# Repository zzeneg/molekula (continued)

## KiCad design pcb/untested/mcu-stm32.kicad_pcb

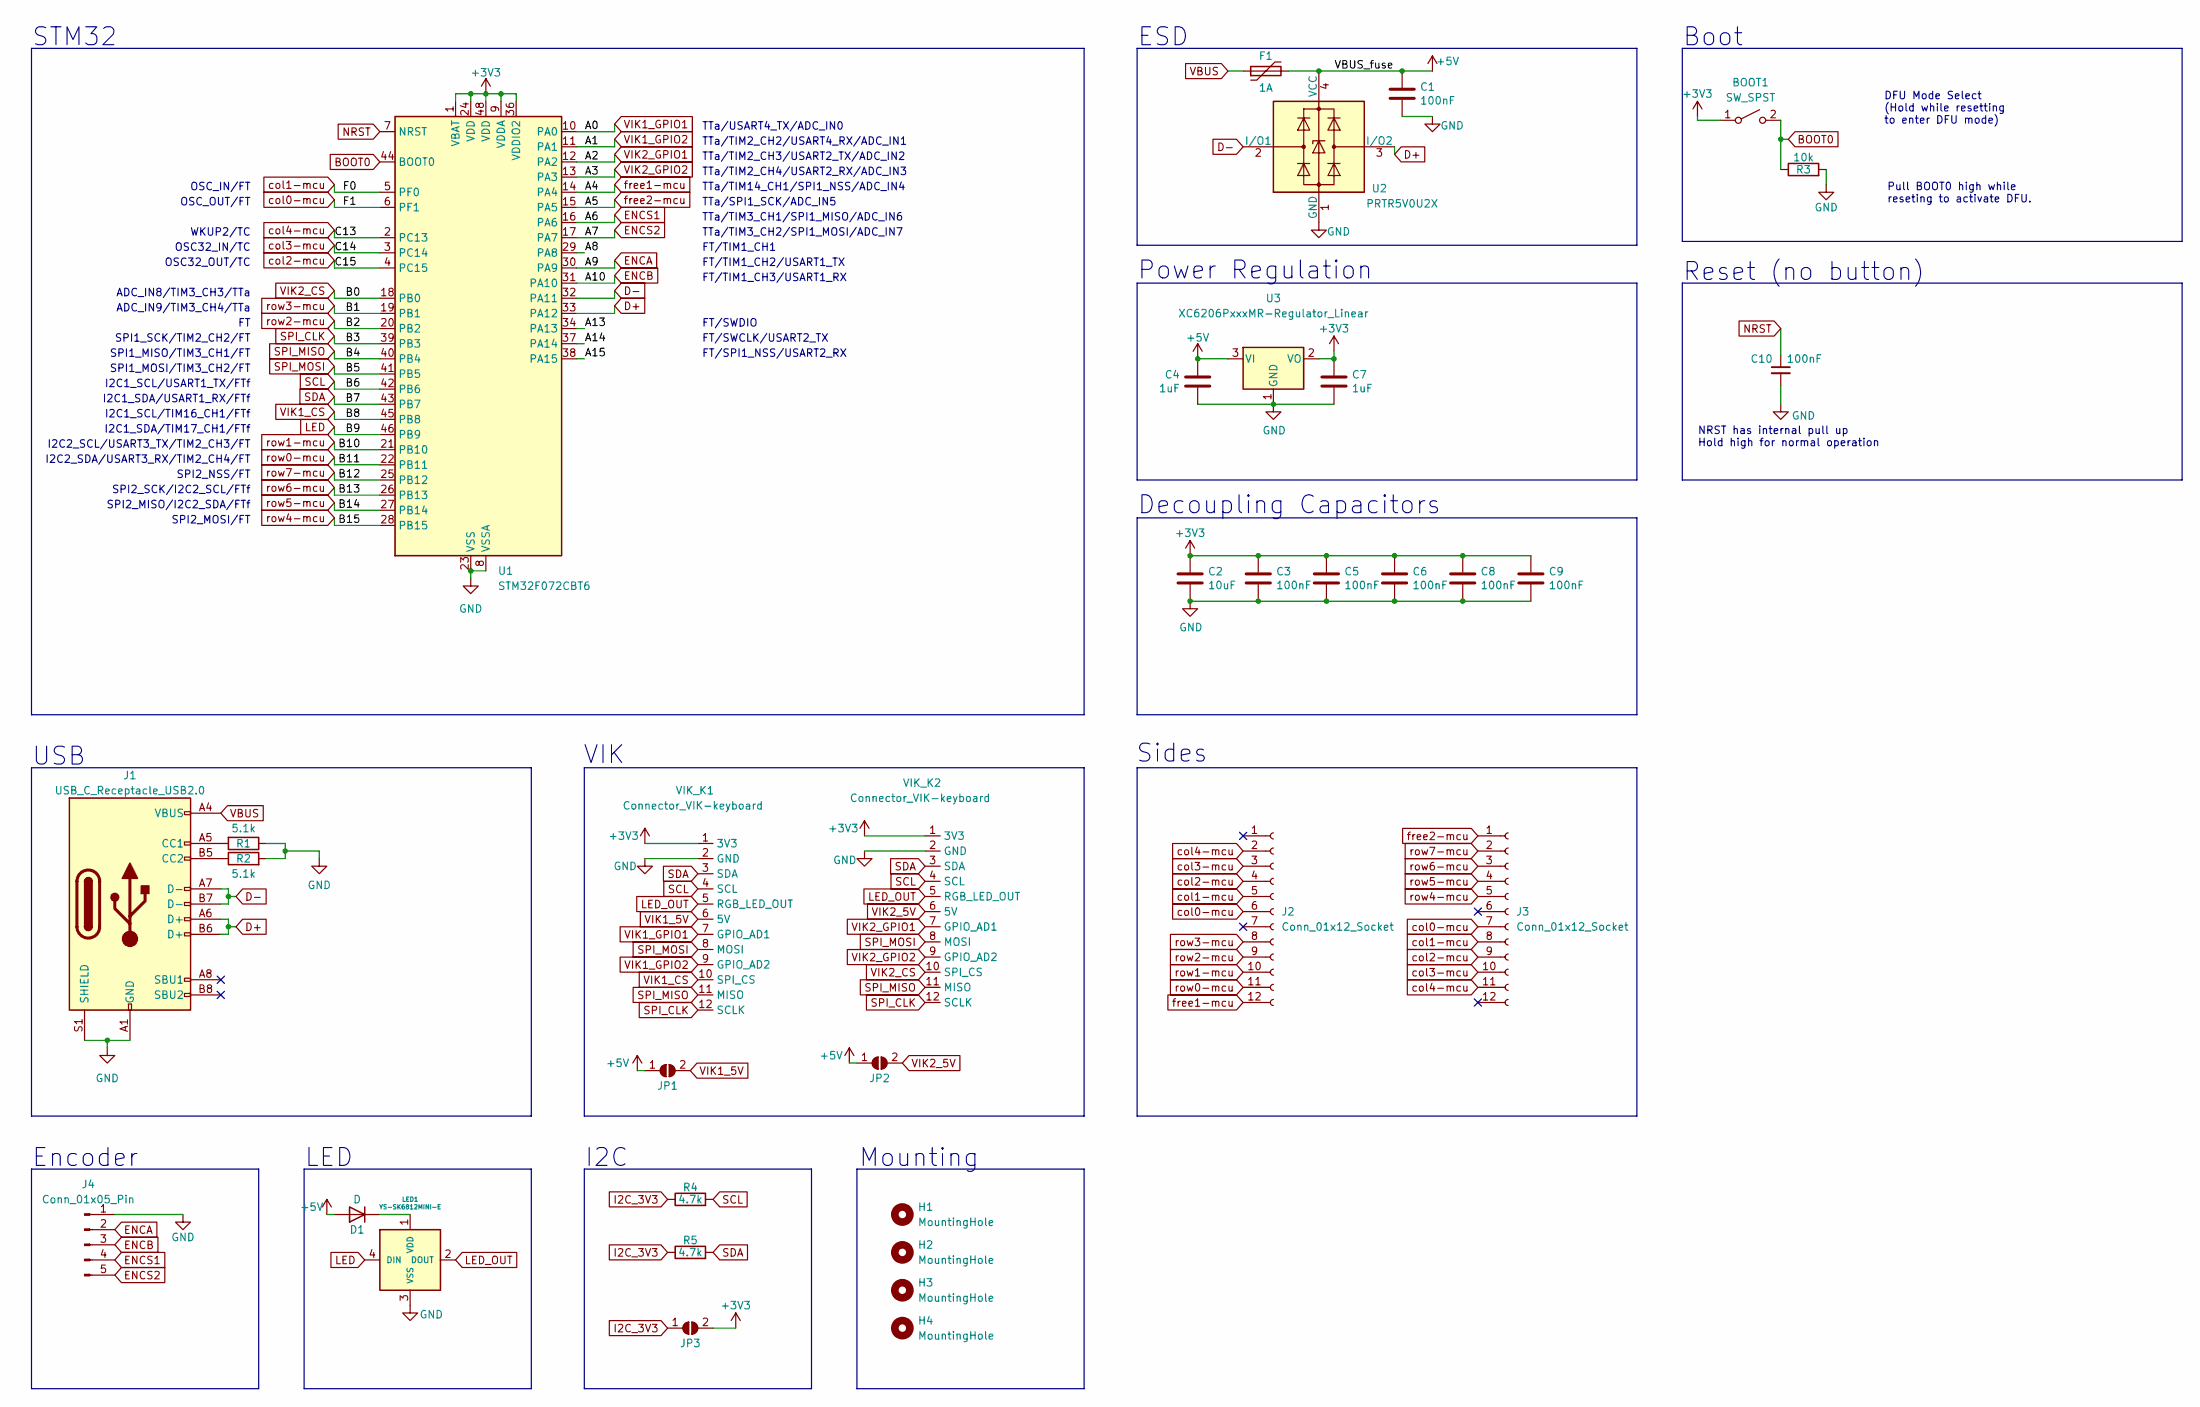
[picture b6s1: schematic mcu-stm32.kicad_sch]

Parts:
BOOT1: SW_SPST; SW_SPST_TL3342
C1, C3, C5, C6, C8, C9, C10: 100nF; C_0805_2012Metric; LCSC C307331
C2: 10uF; C_0805_2012Metric; LCSC C307331
C4, C7: 1uF; C_0805_2012Metric; LCSC C307331
D1: D; Diode_1N4148-SOD123
F1: 1A; Fuse_1206_3216Metric; LCSC C135341
H1, H2, H3, H4: MountingHole; Hole_M2
J1: USB_C_Receptacle_USB2.0; Connector_USB-C-mid-mount-ali; JlcRotOffset 180
J2, J3: Conn_01x12_Socket; Connector_FFC-12pin-0.5mm-horizontal
J4: Conn_01x05_Pin; PinSocket_1x05_P2.54mm_Vertical
JP1, JP2: 5V; SolderJumper-2_P1.3mm_Open_RoundedPad1.0x1.5mm
JP3: VCC; SolderJumper-2_P1.3mm_Open_RoundedPad1.0x1.5mm
LED1: YS-SK6812MINI-E; LED_SK6812-MINI-E
R1, R2: 5.1k; R_0805_2012Metric
R3: 10k; R_0805_2012Metric
R4, R5: 4.7k; R_0805_2012Metric
U1: STM32F072CBT6; LQFP-48_7x7mm_P0.5mm; JlcRotOffset 90
U2: PRTR5V0U2X; SOT-143; LCSC C2827688
U3: XC6206PxxxMR-Regulator_Linear; SOT-23; LCSC C5446
VIK_K1, VIK_K2: Connector_VIK-keyboard; Connector_VIK-horizontal-keyboard

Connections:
+3V3: BOOT1.1 (A), C2.1, C3.1, C5.1, C6.1, C7.1, C8.1, C9.1, JP3.2 (B), U1.1 (VBAT), U1.9 (VDDA), U1.24 (VDD), U1.36 (VDDIO2), U1.48 (VDD), U3.2 (VO), VIK_K1.1 (3V3), VIK_K2.1 (3V3)
+5V: C1.1, C4.1, D1.2 (A), F1.2, JP1.1 (A), JP2.1 (A), U2.4 (VCC), U3.3 (VI)
/A8: U1.29 (PA8)
/A13: U1.34 (PA13)
/A14: U1.37 (PA14)
/A15: U1.38 (PA15)
BOOT0: BOOT1.2 (B), R3.1, U1.44 (BOOT0)
D+: J1.A6 (D+), J1.B6 (D+), U1.33 (PA12), U2.3 (I/O2)
D-: J1.A7 (D-), J1.B7 (D-), U1.32 (PA11), U2.2 (I/O1)
ENCA: J4.2, U1.30 (PA9)
ENCB: J4.3, U1.31 (PA10)
ENCS1: J4.4, U1.16 (PA6)
ENCS2: J4.5, U1.17 (PA7)
GND: C1.2, C2.2, C3.2, C4.2, C5.2, C6.2, C7.2, C8.2, C9.2, C10.2, J1.A1 (GND), J1.A12 (GND), J1.B1 (GND), J1.B12 (GND), J1.S1 (SHIELD), J4.1, LED1.3 (VSS), R1.1, R2.2, R3.2, U1.8 (VSSA), U1.23 (VSS), U1.35 (VSS), U1.47 (VSS), U2.1 (GND), U3.1 (GND), VIK_K1.2 (GND), VIK_K2.2 (GND)
I2C_3V3: JP3.1 (A), R4.1, R5.1
LED: LED1.4 (DIN), U1.46 (PB9)
LED_OUT: LED1.2 (DOUT), VIK_K1.5 (RGB_LED_OUT), VIK_K2.5 (RGB_LED_OUT)
NRST: C10.1, U1.7 (NRST)
unnamed: D1.1 (K), LED1.1 (VDD)
unnamed: J1.A5 (CC1), R1.2
unnamed: J1.B5 (CC2), R2.1
SCL: R4.2, U1.42 (PB6), VIK_K1.4 (SCL), VIK_K2.4 (SCL)
SDA: R5.2, U1.43 (PB7), VIK_K1.3 (SDA), VIK_K2.3 (SDA)
SPI_CLK: U1.39 (PB3), VIK_K1.12 (SCLK), VIK_K2.12 (SCLK)
SPI_MISO: U1.40 (PB4), VIK_K1.11 (MISO), VIK_K2.11 (MISO)
SPI_MOSI: U1.41 (PB5), VIK_K1.8 (MOSI), VIK_K2.8 (MOSI)
VBUS: F1.1, J1.A4 (VBUS), J1.A9 (VBUS), J1.B4 (VBUS), J1.B9 (VBUS)
VIK1_5V: JP1.2 (B), VIK_K1.6 (5V)
VIK1_CS: U1.45 (PB8), VIK_K1.10 (SPI_CS)
VIK1_GPIO1: U1.10 (PA0), VIK_K1.7 (GPIO_AD1)
VIK1_GPIO2: U1.11 (PA1), VIK_K1.9 (GPIO_AD2)
VIK2_5V: JP2.2 (B), VIK_K2.6 (5V)
VIK2_CS: U1.18 (PB0), VIK_K2.10 (SPI_CS)
VIK2_GPIO1: U1.12 (PA2), VIK_K2.7 (GPIO_AD1)
VIK2_GPIO2: U1.13 (PA3), VIK_K2.9 (GPIO_AD2)
col0-mcu: J2.6, J3.7, U1.6 (PF1)
col1-mcu: J2.5, J3.8, U1.5 (PF0)
col2-mcu: J2.4, J3.9, U1.4 (PC15)
col3-mcu: J2.3, J3.10, U1.3 (PC14)
col4-mcu: J2.2, J3.11, U1.2 (PC13)
free1-mcu: J2.12, U1.14 (PA4)
free2-mcu: J3.1, U1.15 (PA5)
row0-mcu: J2.11, U1.22 (PB11)
row1-mcu: J2.10, U1.21 (PB10)
row2-mcu: J2.9, U1.20 (PB2)
row3-mcu: J2.8, U1.19 (PB1)
row4-mcu: J3.5, U1.28 (PB15)
row5-mcu: J3.4, U1.27 (PB14)
row6-mcu: J3.3, U1.26 (PB13)
row7-mcu: J3.2, U1.25 (PB12)

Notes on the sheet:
I2C
TTa/TIM2_CH2/USART4_RX/ADC_IN1
USB
SPI2_MISO/I2C2_SDA/FTf
TTa/TIM2_CH4/USART2_RX/ADC_IN3
I2C1_SCL/USART1_TX/FTf
TTa/TIM14_CH1/SPI1_NSS/ADC_IN4
Boot
SPI2_NSS/FT
TTa/TIM2_CH3/USART2_TX/ADC_IN2
OSC_OUT/FT
ADC_IN8/TIM3_CH3/TTa
WKUP2/TC
NRST has internal pull up Hold high for normal operation
DFU Mode Select (Hold while resetting to enter DFU mode)
FT/TIM1_CH2/USART1_TX
TTa/TIM3_CH1/SPI1_MISO/ADC_IN6
I2C1_SDA/TIM17_CH1/FTf
FT/TIM1_CH1
TTa/TIM3_CH2/SPI1_MOSI/ADC_IN7
Reset (no button)
SPI1_SCK/TIM2_CH2/FT
Encoder
Power Regulation
I2C2_SDA/USART3_RX/TIM2_CH4/FT
OSC32_OUT/TC
OSC32_IN/TC
SPI1_MOSI/TIM3_CH2/FT
Sides
FT/SWDIO
FT/SWCLK/USART2_TX
TTa/SPI1_SCK/ADC_IN5
VIK
I2C2_SCL/USART3_TX/TIM2_CH3/FT
SPI1_MISO/TIM3_CH1/FT
FT/SPI1_NSS/USART2_RX
SPI2_SCK/I2C2_SCL/FTf
LED
SPI2_MOSI/FT
OSC_IN/FT

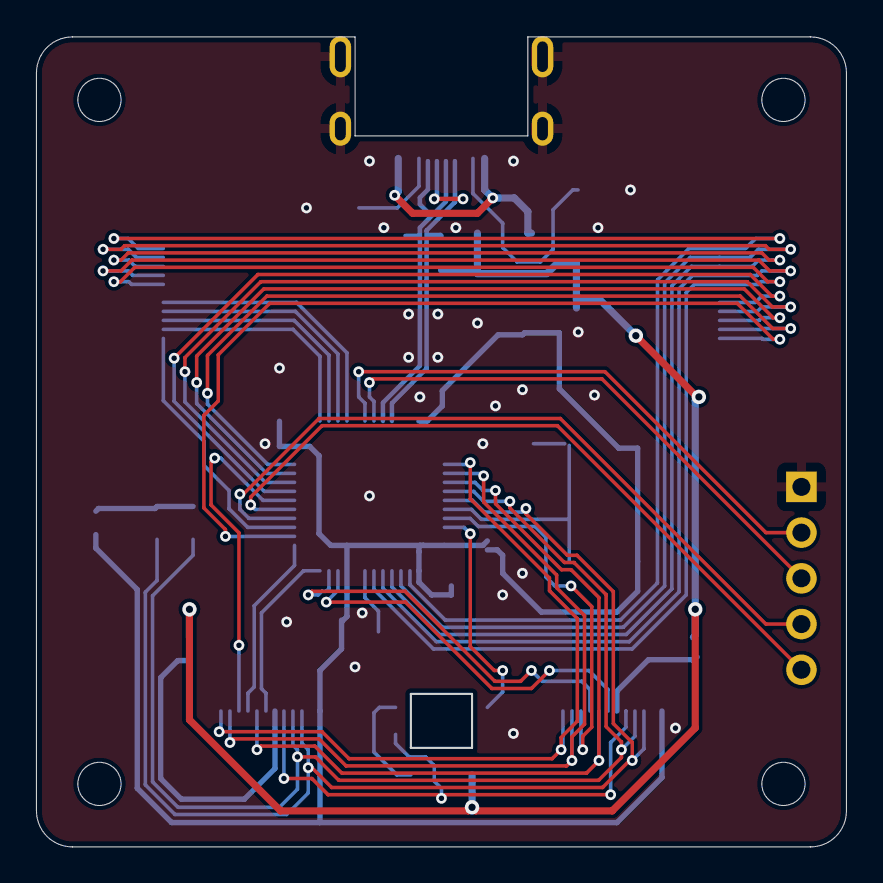
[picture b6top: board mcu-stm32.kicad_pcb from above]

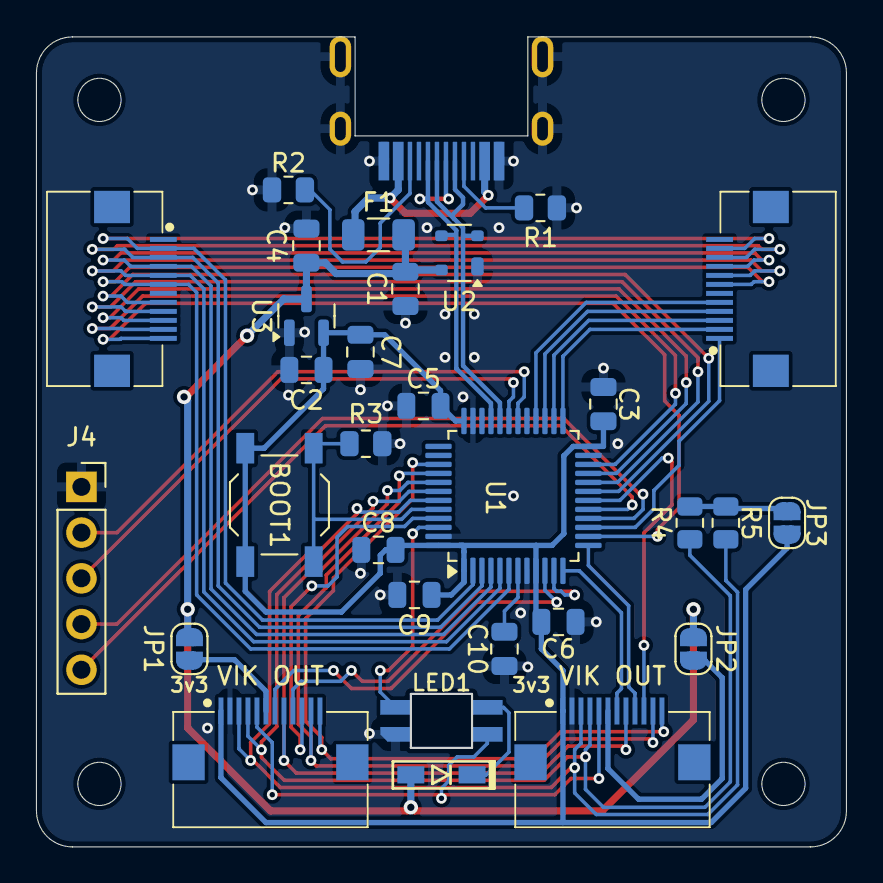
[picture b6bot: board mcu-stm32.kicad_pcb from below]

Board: 2 copper layers, 44.9 x 44.9 mm, 35 parts (31 on the bottom side), 46 nets.

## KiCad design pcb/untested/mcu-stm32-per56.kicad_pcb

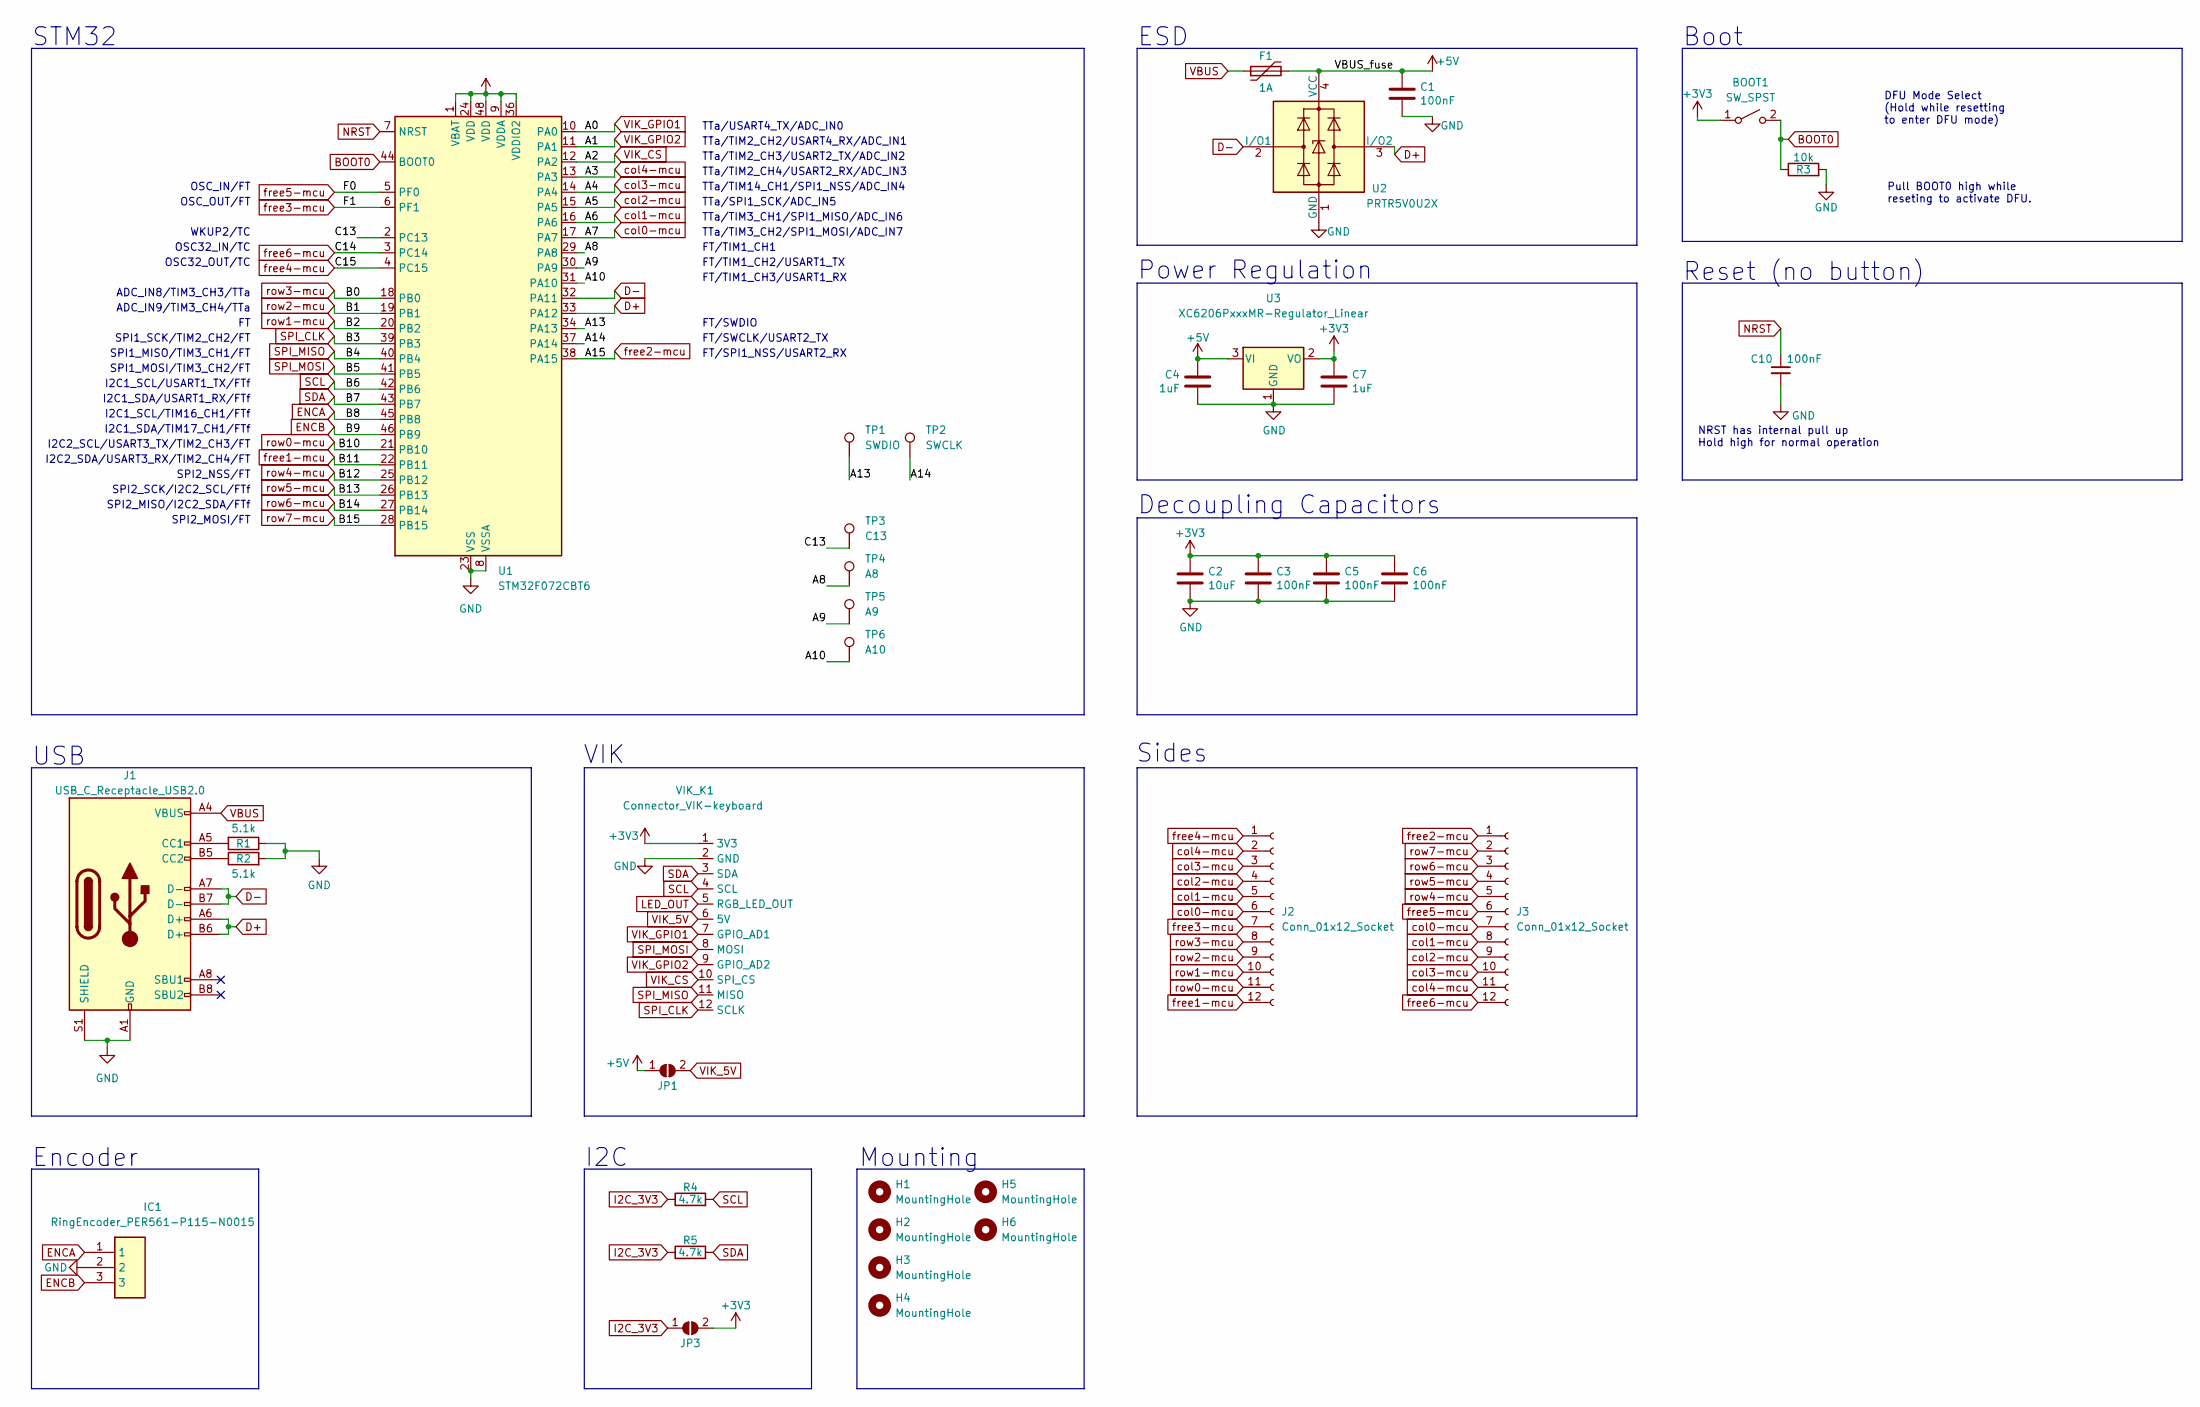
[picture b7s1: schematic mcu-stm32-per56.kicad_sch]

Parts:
BOOT1: SW_SPST; SW_SPST_TL3342
C1, C3, C5, C6, C10: 100nF; C_0805_2012Metric; LCSC C307331
C2: 10uF; C_0805_2012Metric; LCSC C307331
C4, C7: 1uF; C_0805_2012Metric; LCSC C307331
F1: 1A; Fuse_1206_3216Metric; LCSC C135341
H1, H2, H3, H4: MountingHole; Hole_M2-solder-nut-2.5
H5, H6: MountingHole; Hole_M2
IC1: RingEncoder_PER561-P115-N0015; Manufacturer_Part_Number PER561-P115-N0015; Mouser Part Number 652-PER561P115N0015
J1: USB_C_Receptacle_USB2.0; Connector_HRO-TYPE-C-31-M-12; JlcRotOffset 180
J2, J3: Conn_01x12_Socket; Connector_FFC-12pin-0.5mm-horizontal
JP1: VIK 5V; SolderJumper-2_P1.3mm_Open_RoundedPad1.0x1.5mm
JP3: I2C PullUp; SolderJumper-2_P1.3mm_Open_RoundedPad1.0x1.5mm
R1, R2: 5.1k; R_0805_2012Metric
R3: 10k; R_0805_2012Metric
R4, R5: 4.7k; R_0805_2012Metric
TP1: SWDIO; TestPoint_Pad_D1.5mm
TP2: SWCLK; TestPoint_Pad_D1.5mm
TP3: C13; TestPoint_THTPad_D2.0mm_Drill1.0mm
TP4: A8; TestPoint_THTPad_D2.0mm_Drill1.0mm
TP5: A9; TestPoint_THTPad_D2.0mm_Drill1.0mm
TP6: A10; TestPoint_THTPad_D2.0mm_Drill1.0mm
U1: STM32F072CBT6; LQFP-48_7x7mm_P0.5mm; JlcRotOffset 90
U2: PRTR5V0U2X; SOT-143; LCSC C2827688
U3: XC6206PxxxMR-Regulator_Linear; SOT-23; LCSC C5446
VIK_K1: Connector_VIK-keyboard; Connector_VIK-horizontal-keyboard

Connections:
+3V3: BOOT1.1 (A), C2.1, C3.1, C5.1, C6.1, C7.1, JP3.2 (B), U1.1 (VBAT), U1.9 (VDDA), U1.24 (VDD), U1.36 (VDDIO2), U1.48 (VDD), U3.2 (VO), VIK_K1.1 (3V3)
+5V: C1.1, C4.1, F1.2, JP1.1 (A), U2.4 (VCC), U3.3 (VI)
/A8: TP4.1, U1.29 (PA8)
/A9: TP5.1, U1.30 (PA9)
/A10: TP6.1, U1.31 (PA10)
/A13: TP1.1, U1.34 (PA13)
/A14: TP2.1, U1.37 (PA14)
/C13: TP3.1, U1.2 (PC13)
BOOT0: BOOT1.2 (B), R3.1, U1.44 (BOOT0)
D+: J1.A6 (D+), J1.B6 (D+), U1.33 (PA12), U2.3 (I/O2)
D-: J1.A7 (D-), J1.B7 (D-), U1.32 (PA11), U2.2 (I/O1)
ENCA: IC1.1, U1.45 (PB8)
ENCB: IC1.3, U1.46 (PB9)
GND: C1.2, C2.2, C3.2, C4.2, C5.2, C6.2, C7.2, C10.2, IC1.2, J1.A1 (GND), J1.A12 (GND), J1.B1 (GND), J1.B12 (GND), J1.S1 (SHIELD), R1.1, R2.2, R3.2, U1.8 (VSSA), U1.23 (VSS), U1.35 (VSS), U1.47 (VSS), U2.1 (GND), U3.1 (GND), VIK_K1.2 (GND)
I2C_3V3: JP3.1 (A), R4.1, R5.1
LED_OUT: VIK_K1.5 (RGB_LED_OUT)
NRST: C10.1, U1.7 (NRST)
unnamed: J1.A5 (CC1), R1.2
unnamed: J1.B5 (CC2), R2.1
SCL: R4.2, U1.42 (PB6), VIK_K1.4 (SCL)
SDA: R5.2, U1.43 (PB7), VIK_K1.3 (SDA)
SPI_CLK: U1.39 (PB3), VIK_K1.12 (SCLK)
SPI_MISO: U1.40 (PB4), VIK_K1.11 (MISO)
SPI_MOSI: U1.41 (PB5), VIK_K1.8 (MOSI)
VBUS: F1.1, J1.A4 (VBUS), J1.A9 (VBUS), J1.B4 (VBUS), J1.B9 (VBUS)
VIK_5V: JP1.2 (B), VIK_K1.6 (5V)
VIK_CS: U1.12 (PA2), VIK_K1.10 (SPI_CS)
VIK_GPIO1: U1.10 (PA0), VIK_K1.7 (GPIO_AD1)
VIK_GPIO2: U1.11 (PA1), VIK_K1.9 (GPIO_AD2)
col0-mcu: J2.6, J3.7, U1.17 (PA7)
col1-mcu: J2.5, J3.8, U1.16 (PA6)
col2-mcu: J2.4, J3.9, U1.15 (PA5)
col3-mcu: J2.3, J3.10, U1.14 (PA4)
col4-mcu: J2.2, J3.11, U1.13 (PA3)
free1-mcu: J2.12, U1.22 (PB11)
free2-mcu: J3.1, U1.38 (PA15)
free3-mcu: J2.7, U1.6 (PF1)
free4-mcu: J2.1, U1.4 (PC15)
free5-mcu: J3.6, U1.5 (PF0)
free6-mcu: J3.12, U1.3 (PC14)
row0-mcu: J2.11, U1.21 (PB10)
row1-mcu: J2.10, U1.20 (PB2)
row2-mcu: J2.9, U1.19 (PB1)
row3-mcu: J2.8, U1.18 (PB0)
row4-mcu: J3.5, U1.25 (PB12)
row5-mcu: J3.4, U1.26 (PB13)
row6-mcu: J3.3, U1.27 (PB14)
row7-mcu: J3.2, U1.28 (PB15)

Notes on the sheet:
I2C
TTa/TIM2_CH2/USART4_RX/ADC_IN1
USB
SPI2_MISO/I2C2_SDA/FTf
TTa/TIM2_CH4/USART2_RX/ADC_IN3
I2C1_SCL/USART1_TX/FTf
TTa/TIM14_CH1/SPI1_NSS/ADC_IN4
Boot
SPI2_NSS/FT
TTa/TIM2_CH3/USART2_TX/ADC_IN2
OSC_OUT/FT
ADC_IN8/TIM3_CH3/TTa
WKUP2/TC
NRST has internal pull up Hold high for normal operation
DFU Mode Select (Hold while resetting to enter DFU mode)
FT/TIM1_CH2/USART1_TX
TTa/TIM3_CH1/SPI1_MISO/ADC_IN6
I2C1_SDA/TIM17_CH1/FTf
FT/TIM1_CH1
TTa/TIM3_CH2/SPI1_MOSI/ADC_IN7
Reset (no button)
SPI1_SCK/TIM2_CH2/FT
Encoder
Power Regulation
I2C2_SDA/USART3_RX/TIM2_CH4/FT
OSC32_OUT/TC
OSC32_IN/TC
SPI1_MOSI/TIM3_CH2/FT
Sides
FT/SWDIO
FT/SWCLK/USART2_TX
TTa/SPI1_SCK/ADC_IN5
VIK
I2C2_SCL/USART3_TX/TIM2_CH3/FT
SPI1_MISO/TIM3_CH1/FT
FT/SPI1_NSS/USART2_RX
SPI2_SCK/I2C2_SCL/FTf
SPI2_MOSI/FT
OSC_IN/FT
ESD

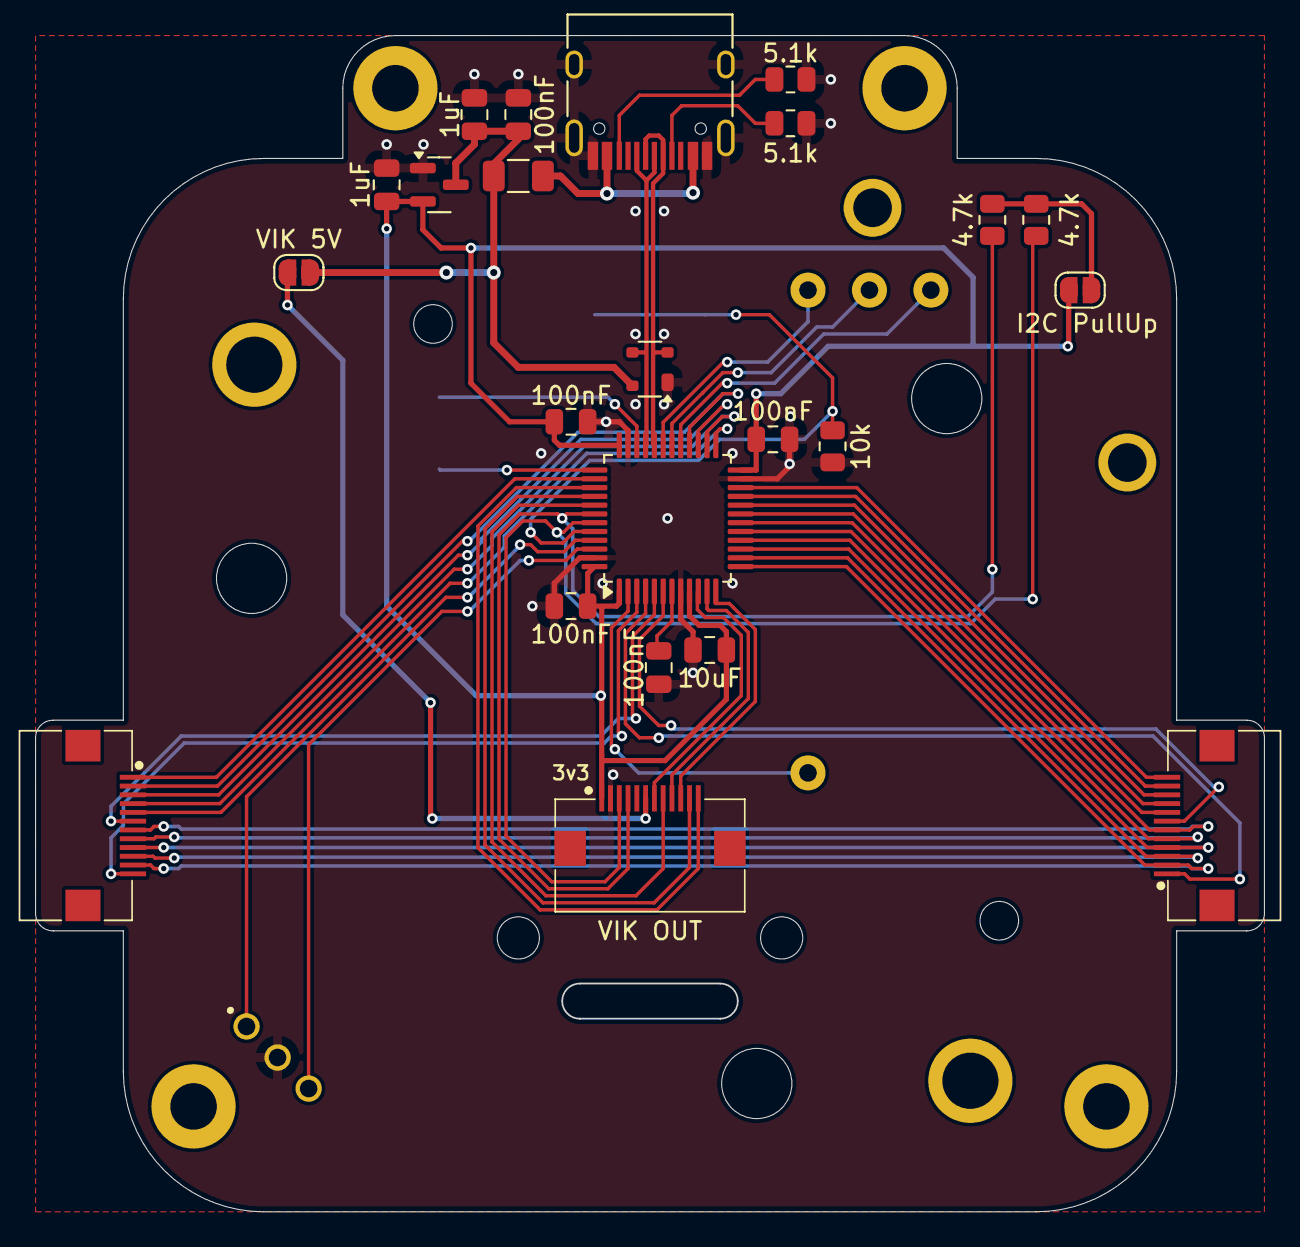
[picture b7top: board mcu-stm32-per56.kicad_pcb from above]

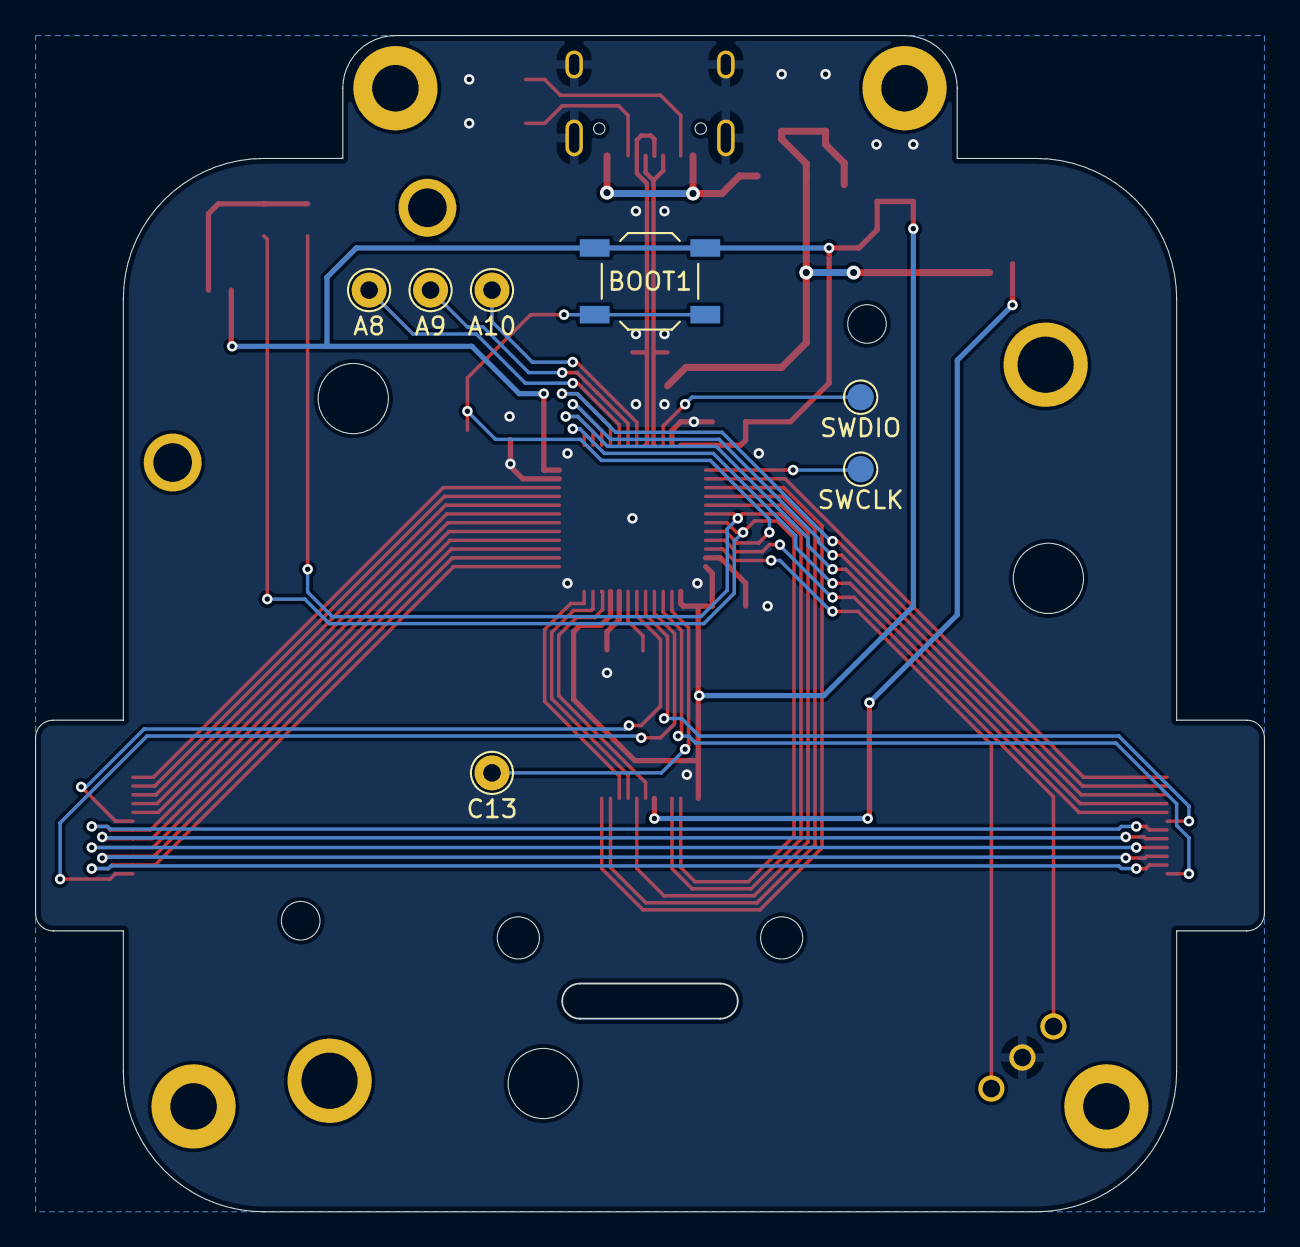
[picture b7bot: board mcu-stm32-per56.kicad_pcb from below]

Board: 2 copper layers, 70.0 x 67.0 mm, 37 parts (7 on the bottom side), 47 nets.

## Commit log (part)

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2024-05-08 first draft
2024-06-11 second draft
2024-06-28 update pin names
2024-07-13 update case and main pcb
2024-08-31 fix headset depth, increase side tolerance
2024-10-22 move thumbs to inner side
2024-10-25 stm32 mcu
2024-11-01 pcba version
2024-11-01 add 3d components
2024-11-01 replace ec11 with ec12
2024-11-01 small updates
2024-11-02 add chocV2 case
2024-11-04 chamfered case
2024-11-10 rework stl export
2024-11-17 add stm32-per56
2024-11-17 add 3-part case
2024-11-20 improve case (mx version), rename files
2024-11-26 add keycaps
2024-11-26 add logo, move case files into subfolders
2024-11-26 2-part case: increase tolerances, small improvements
2024-11-28 2-part case: shell bottom
2024-12-10 rework pcb for per56
2024-12-13 2part case: - bigger choc cutouts - smaller knob hole - thinner logo
2024-12-14 2part case: update logo
2025-01-04 remove untested files
2025-01-04 restructure files
2025-01-05 draft readme
2025-01-05 improve combined pcb
2025-01-05 finalize readme
2025-09-10 draft 3-part case
2026-01-25 update case, add keycaps
2026-05-30 update stls
2026-05-30 add molekula3
2026-06-02 readme and images for molekula3
